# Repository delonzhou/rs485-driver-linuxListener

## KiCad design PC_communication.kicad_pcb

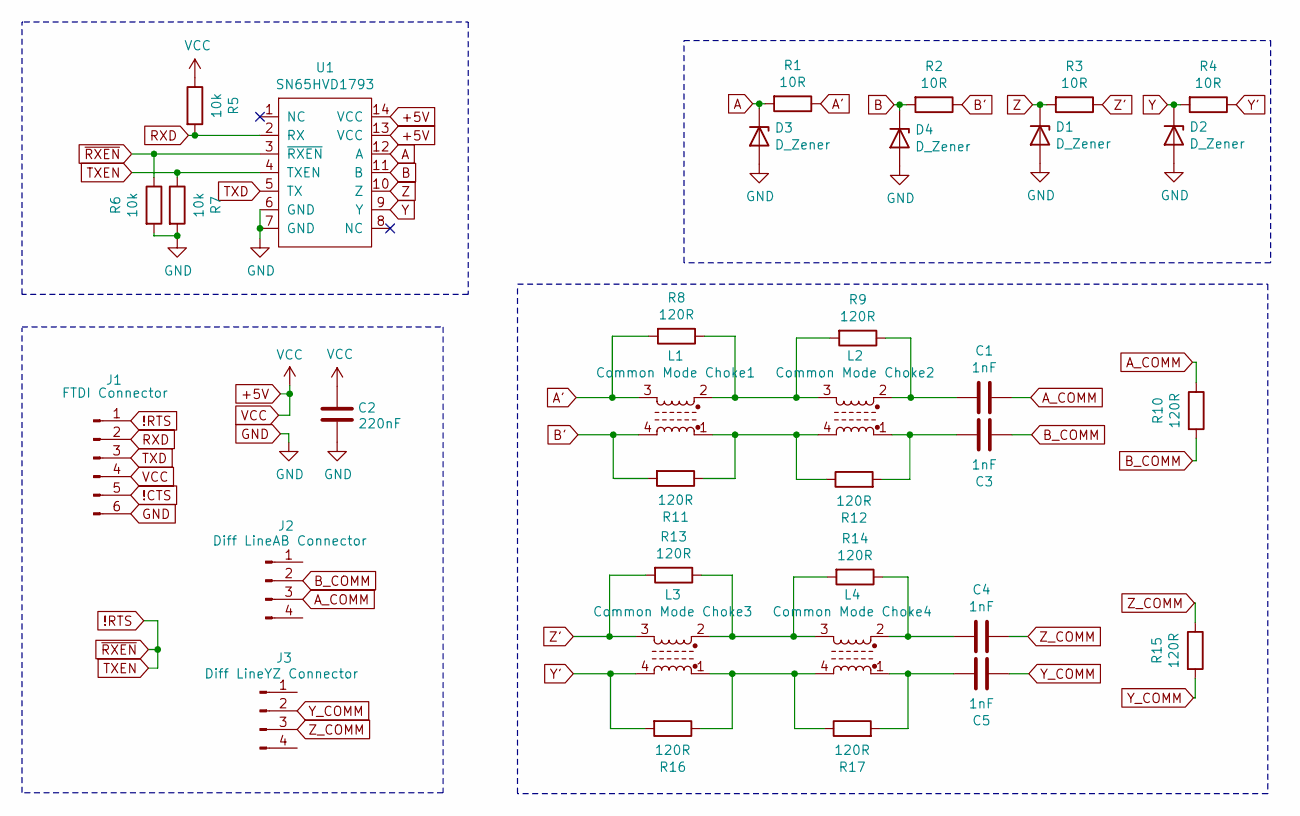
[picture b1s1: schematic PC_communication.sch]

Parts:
C1, C3, C4, C5: 1nF; C_1206_3216Metric
C2: 220nF; C_1206_3216Metric
D1, D2, D3, D4: D_Zener; D_SOD-323
J1: FTDI Connector; PinHeader_1x06_P2.54mm_Vertical
J2: Diff LineAB Connector; 2178710-4
J3: Diff LineYZ Connector; 2178710-4
L1: Common Mode Choke1; 744242471
L2: Common Mode Choke2; ACT45B-101-2P
L3: Common Mode Choke3; 744242471
L4: Common Mode Choke4; ACT45B-101-2P
R1, R2, R3, R4: 10R; R_1206_3216Metric
R5, R6, R7: 10k; R_1206_3216Metric
R8, R9, R10, R11, R12, R13, R14, R15, R16, R17: 120R; R_1206_3216Metric
U1: SN65HVD1793; SOIC-14_3.9x8.7mm_P1.27mm

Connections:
!CTS: J1.5
!RTS: J1.1, R6.1, R7.1, U1.3 (~RXEN), U1.4 (TXEN)
+5V: C2.2, J1.4, R5.1, U1.13 (VCC), U1.14 (VCC)
A: D3.1 (K), R1.2, U1.12 (A)
A': L1.3, R1.1, R8.2
A_COMM: C1.1, J2.3, R10.1
B: D4.1 (K), R2.2, U1.11 (B)
B': L1.4, R2.1, R11.2
B_COMM: C3.2, J2.2, R10.2
GND: C2.1, D1.2 (A), D2.2 (A), D3.2 (A), D4.2 (A), J1.6, R6.2, R7.2, U1.6 (GND), U1.7 (GND)
unnamed: C1.2, L2.2, R9.1
unnamed: C3.1, L2.1, R12.2
unnamed: C4.2, L4.2, R14.1
unnamed: C5.1, L4.1, R17.2
unnamed: L1.1, L2.4, R11.1, R12.1
unnamed: L1.2, L2.3, R8.1, R9.2
unnamed: L3.1, L4.4, R16.1, R17.1
unnamed: L3.2, L4.3, R13.1, R14.2
RXD: J1.2, R5.2, U1.2 (RX)
TXD: J1.3, U1.5 (TX)
Y: D2.1 (K), R4.2, U1.9 (Y)
Y': L3.4, R4.1, R16.2
Y_COMM: C5.2, J3.2, R15.2
Z: D1.1 (K), R3.2, U1.10 (Z)
Z': L3.3, R3.1, R13.2
Z_COMM: C4.1, J3.3, R15.1

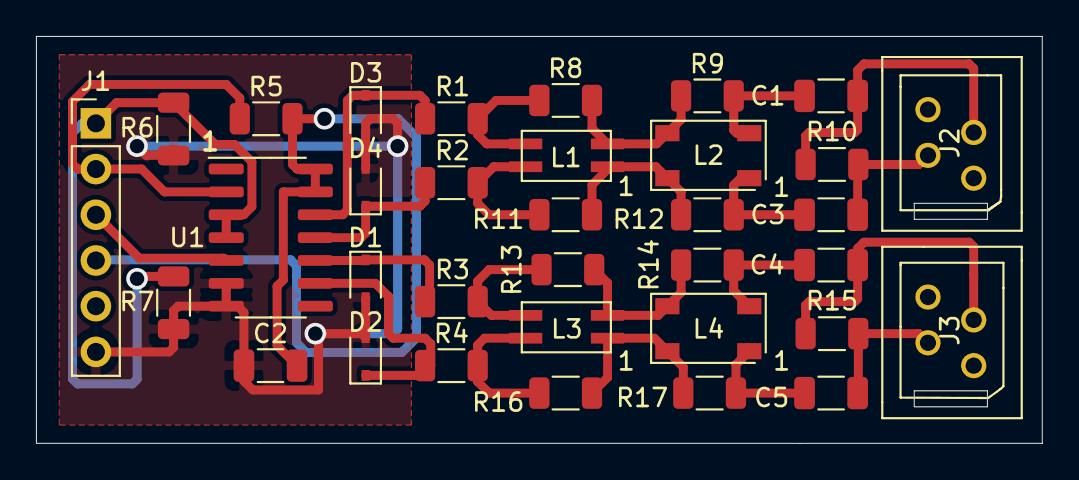
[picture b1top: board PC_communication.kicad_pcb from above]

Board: 2 copper layers, 55.9 x 22.6 mm, 34 parts (0 on the bottom side), 25 nets.
